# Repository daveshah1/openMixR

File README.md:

# openMixR 4k Mixed Reality Headset

openMixR is an open software/hardware mixed reality headset powered by an Artix-7 FPGA. It combines a high-resolution (4k) virtual reality headset with
4k cameras and a powerful FPGA to provide augmented reality experiences.

## Current Status

Last year as a university group project a low resolution prototype was built, capable of demos
including a 2D Minecraft game and overlaying content from an HDMI input.

PCB design for revision 1 of the 4k version - which this repo is for - has been finished and PCBs have now arrived. FPGA HDL for the cameras has been developed and tested (albeit
  with a different camera model only capable of 4k30, see [this repo](https://github.com/daveshah1/CSI2Rx)), and HDL for basic LCD functionality has been written
and undergone basic testing. To run the display at 4k will require feeding it with VESA DSC compressed video; code for
this is far from complete so I will be using the display at first in a mode where it upscales from 1080p - which
still looks a lot nicer than a native 1080p LCD. Current LCD code is [here](https://github.com/daveshah1/DSITx).

I am now in the process of testing the PCBs and writing a simple AR demo using the LCD and cameras. At present no breaking
issues in the rev 1.0 PCB have arisen although do take note a few minor errata points - see the hardware folder.

I am also working on a custom HLS tool, not yet released, that will be used to create much of the FPGA processing
code that runs on the headset. An early version of this was used for the aforementioned low res demos.

## Hardware Features

The main components of the hardware are:

 - 4k LCD repurposed from Z5 premium (AUO H546UAN01.0 or unknown Sharp part) on a subassembly allowing different LCDs to be used in the future
 - Dual OV16825 cameras, also on a subassembly so other cameras - in particular I am looking into the Sony IMX318 - could be used
 - Artix-7 FPGA (currently XC7A200T-3FBG484E but cheaper variants could be used)
 - Allwinner A64 quad-core ARM applications processor (with basic GPU for 3D rendering)
 - 512MB of DDR3 attached to the FPGA and 1GB attached to the A64 processor
 - WiFi and Bluetooth
 - USB-C for power, data and DisplayPort video

A photo of the assembled mainboard PCB is below:

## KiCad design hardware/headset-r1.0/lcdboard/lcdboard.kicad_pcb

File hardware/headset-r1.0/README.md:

# Hardware for openMixR 1.0

All of the hardware is designed in KiCad 4.0, in the spirit of open source.

- *mainboard* is the headset mainboard, containing the FPGA and processor. It is a 150x90mm 8-layer board
with a minimum track/space of 4mil and a controlled impedance requirement.
- *camboard* is the OV16825 camera subassembly
- *lcdboard* is the Z5 Premium LCD subassembly
- *usbbase* is a board that combines power, USB 2.0 data and Displayport into a USB-C connection,
so openMixR can be used if your computer doesn't support USB-C.

In addition, all of the libraries needed are included. Schematic component libraries are inside the
board folders, with the exception  of *customconn* which is the custom LCD and camera connectors that
interconnect the mainboard and subassemblies. *parts.pretty* contains all of the custom footprints; and *3d*
contains 3D models for many of the components used (for the most part converted from the models provided by their vendors).

PDF schematics are included for all of the boards, if you don't want to install KiCad. Gerbers are also included for all of the boards.

A bill of materials, placement data and impedance control diagrams are also included for the mainboard.

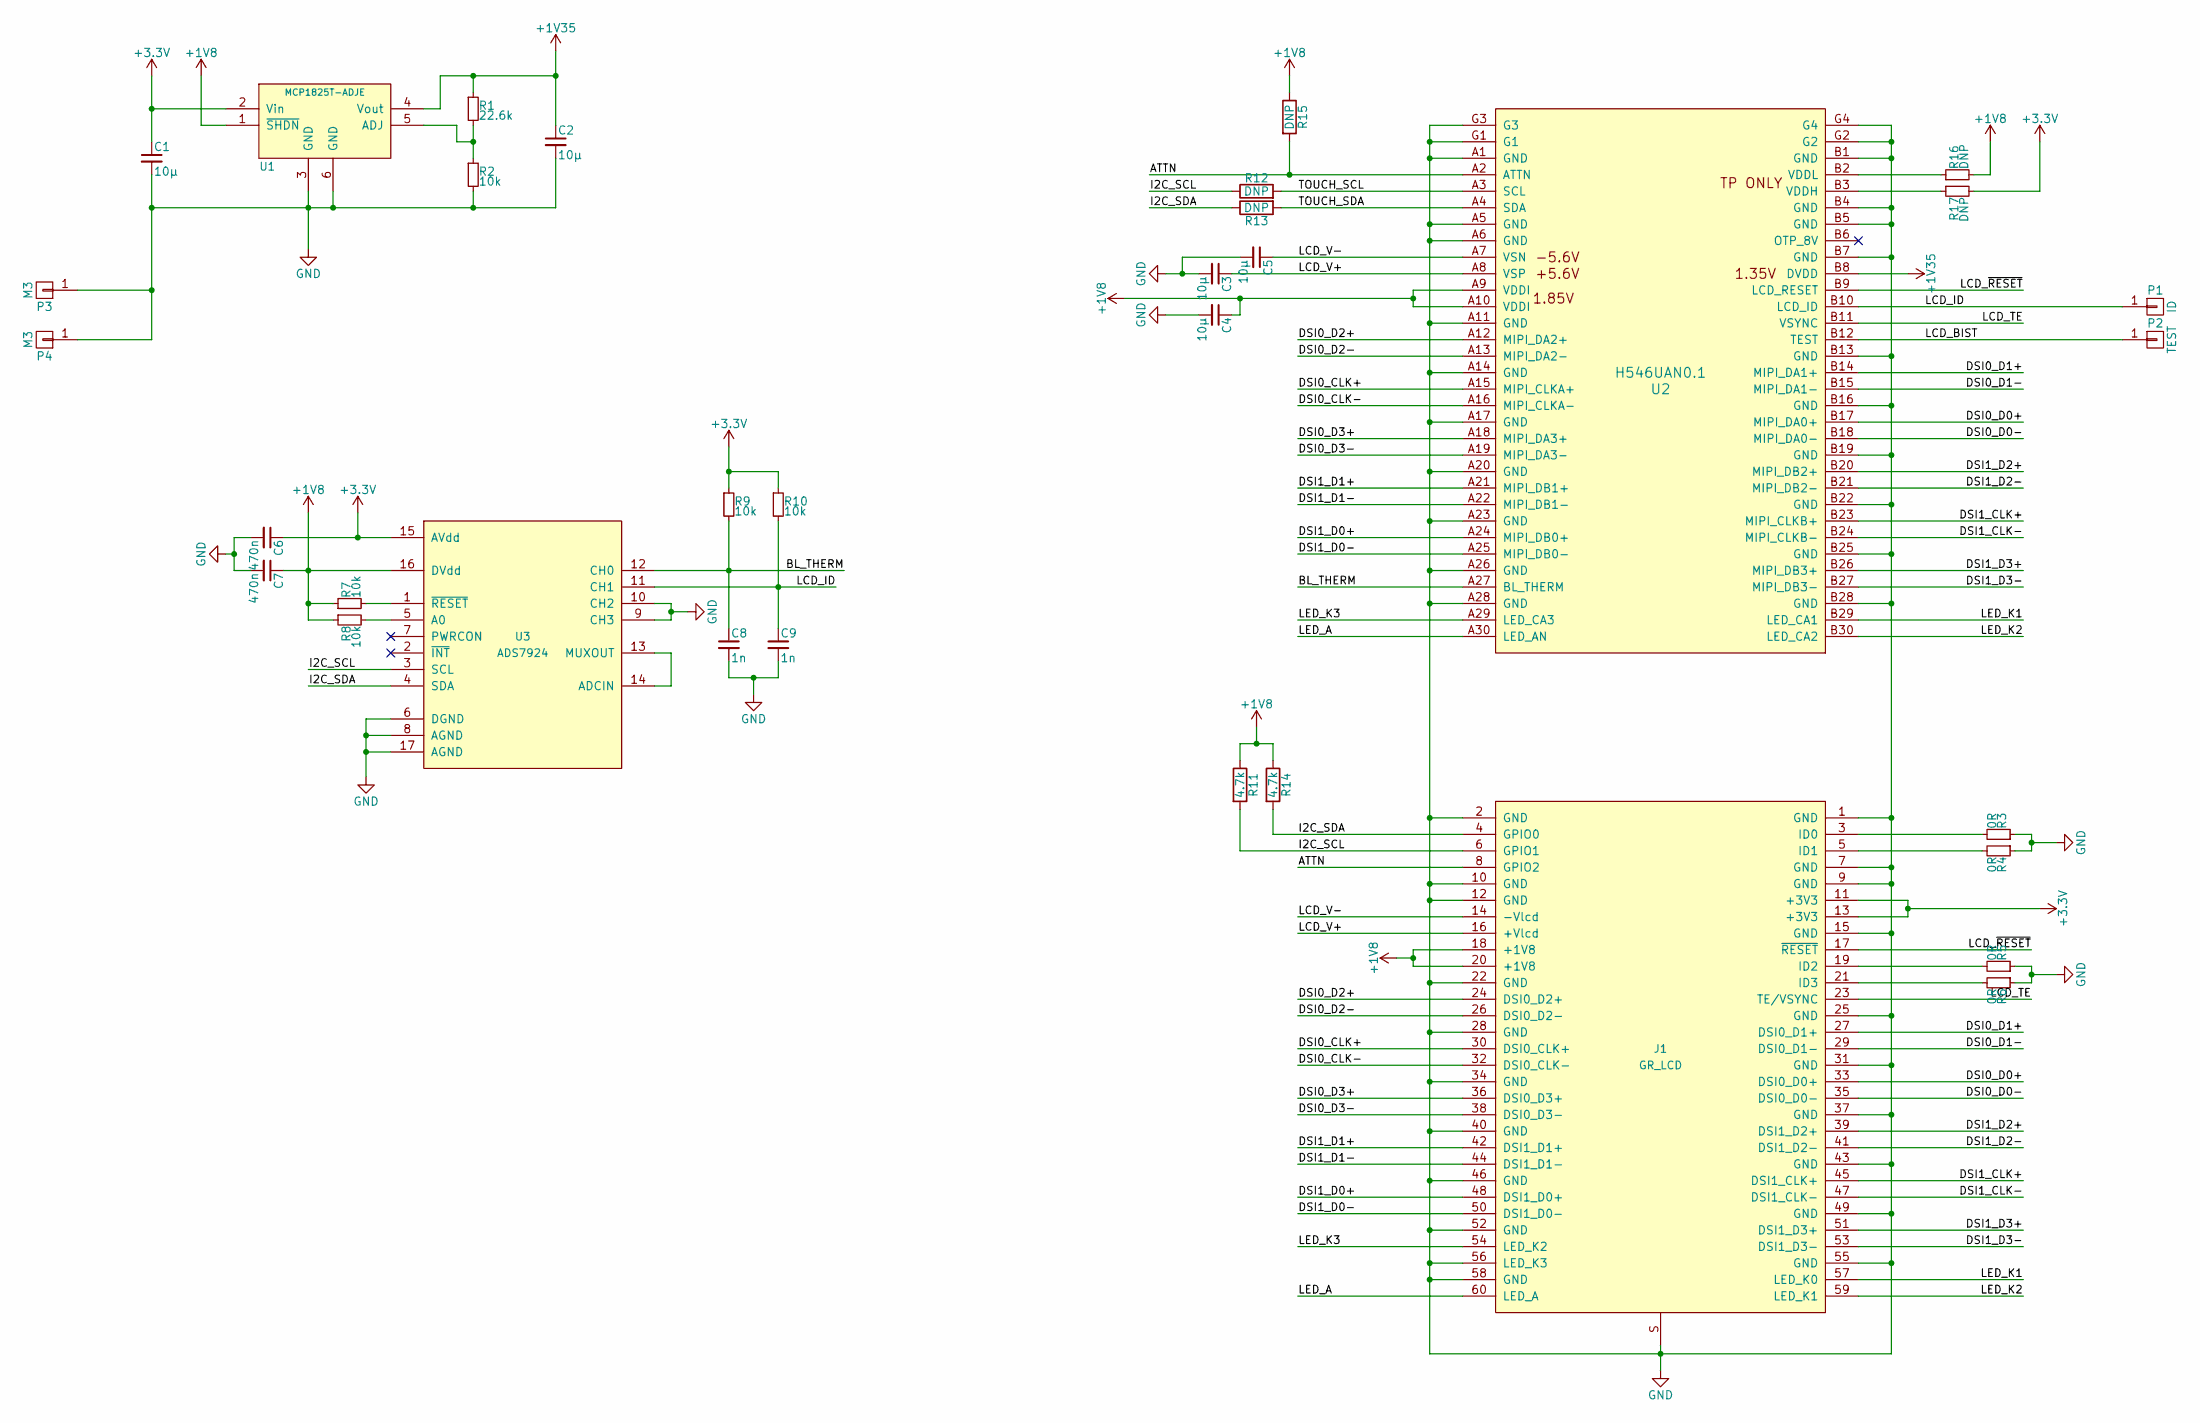
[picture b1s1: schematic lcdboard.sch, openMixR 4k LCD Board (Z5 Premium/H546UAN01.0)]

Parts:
C1, C2, C3, C4, C5: 10µ; C_0805
C6, C7: 470n; C_0402
C8, C9: 1n; C_0402
J1: GR_LCD; DF17(2.0)-60DP-0.5V(57)
P1: ID; Measurement_Point_Square-SMD-Pad_Big
P2: TEST; Measurement_Point_Square-SMD-Pad_Big
P3, P4: M3; M3_HOLE
R1: 22.6k; R_0402
R2, R7, R8, R9, R10: 10k; R_0402
R3, R4, R5, R6: 0R; R_0402
R11, R14: 4.7k; R_0402
R12, R13, R15, R16, R17: DNP; R_0402
U1: MCP1825T-ADJE; SOT-223-6
U2: H546UAN0.1; 60pin-0.35mm
U3: ADS7924; QFN-16-1EP_3x3mm_Pitch0.5mm

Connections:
+1V8: C4.1, C7.1, J1.18 (+1V8), J1.20 (+1V8), R7.1, R8.1, R11.1, R14.1, R15.1, R16.2, U1.1 (~SHDN), U2.A9 (VDDI), U2.A10 (VDDI), U3.16 (DVdd)
+1V35: C2.1, R1.1, U1.4 (Vout), U2.B8 (DVDD)
+3V3: C1.1, C6.1, J1.11 (+3V3), J1.13 (+3V3), R9.1, R10.1, R17.2, U1.2 (Vin), U3.15 (AVdd)
/ATTN: J1.8 (GPIO2), R15.2, U2.A2 (ATTN)
/BL_THERM: C8.1, R9.2, U2.A27 (BL_THERM), U3.12 (CH0)
/DSI0_CLK+: J1.30 (DSI0_CLK+), U2.A15 (MIPI_CLKA+)
/DSI0_CLK-: J1.32 (DSI0_CLK-), U2.A16 (MIPI_CLKA-)
/DSI0_D0+: J1.33 (DSI0_D0+), U2.B17 (MIPI_DA0+)
/DSI0_D0-: J1.35 (DSI0_D0-), U2.B18 (MIPI_DA0-)
/DSI0_D1+: J1.27 (DSI0_D1+), U2.B14 (MIPI_DA1+)
/DSI0_D1-: J1.29 (DSI0_D1-), U2.B15 (MIPI_DA1-)
/DSI0_D2+: J1.24 (DSI0_D2+), U2.A12 (MIPI_DA2+)
/DSI0_D2-: J1.26 (DSI0_D2-), U2.A13 (MIPI_DA2-)
/DSI0_D3+: J1.36 (DSI0_D3+), U2.A18 (MIPI_DA3+)
/DSI0_D3-: J1.38 (DSI0_D3-), U2.A19 (MIPI_DA3-)
/DSI1_CLK+: J1.45 (DSI1_CLK+), U2.B23 (MIPI_CLKB+)
/DSI1_CLK-: J1.47 (DSI1_CLK-), U2.B24 (MIPI_CLKB-)
/DSI1_D0+: J1.48 (DSI1_D0+), U2.A24 (MIPI_DB0+)
/DSI1_D0-: J1.50 (DSI1_D0-), U2.A25 (MIPI_DB0-)
/DSI1_D1+: J1.42 (DSI1_D1+), U2.A21 (MIPI_DB1+)
/DSI1_D1-: J1.44 (DSI1_D1-), U2.A22 (MIPI_DB1-)
/DSI1_D2+: J1.39 (DSI1_D2+), U2.B20 (MIPI_DB2+)
/DSI1_D2-: J1.41 (DSI1_D2-), U2.B21 (MIPI_DB2-)
/DSI1_D3+: J1.51 (DSI1_D3+), U2.B26 (MIPI_DB3+)
/DSI1_D3-: J1.53 (DSI1_D3-), U2.B27 (MIPI_DB3-)
/I2C_SCL: J1.6 (GPIO1), R11.2, R12.1, U3.3 (SCL)
/I2C_SDA: J1.4 (GPIO0), R13.1, R14.2, U3.4 (SDA)
/LCD_BIST: P2.1, U2.B12 (TEST)
/LCD_ID: C9.1, P1.1, R10.2, U2.B10 (LCD_ID), U3.11 (CH1)
/LCD_TE: J1.23 (TE/VSYNC), U2.B11 (VSYNC)
/LCD_V+: C3.1, J1.16 (+Vlcd), U2.A8 (VSP)
/LCD_V-: C5.1, J1.14 (-Vlcd), U2.A7 (VSN)
/LCD_~RESET: J1.17 (~RESET), U2.B9 (LCD_RESET)
/LED_A: J1.60 (LED_A), U2.A30 (LED_AN)
/LED_K1: J1.57 (LED_K0), U2.B29 (LED_CA1)
/LED_K2: J1.59 (LED_K1), U2.B30 (LED_CA2)
/LED_K3: J1.54 (LED_K2), U2.A29 (LED_CA3)
/TOUCH_SCL: R12.2, U2.A3 (SCL)
/TOUCH_SDA: R13.2, U2.A4 (SDA)
GND: C1.2, C2.2, C3.2, C4.2, C5.2, C6.2, C7.2, C8.2, C9.2, J1.1 (GND), J1.2 (GND), J1.7 (GND), J1.9 (GND), J1.10 (GND), J1.12 (GND), J1.15 (GND), J1.22 (GND), J1.25 (GND), J1.28 (GND), J1.31 (GND), J1.34 (GND), J1.37 (GND), J1.40 (GND), J1.43 (GND), J1.46 (GND), J1.49 (GND), J1.52 (GND), J1.55 (GND), J1.56 (LED_K3), J1.58 (GND), J1.S, P3.1, P4.1, R2.2, R3.1, R4.1, R5.1, R6.1, U1.3 (GND), U1.6 (GND), U2.A1 (GND), U2.A5 (GND), U2.A6 (GND), U2.A11 (GND), U2.A14 (GND), U2.A17 (GND), U2.A20 (GND), U2.A23 (GND), U2.A26 (GND), U2.A28 (GND), U2.B1 (GND), U2.B4 (GND), U2.B5 (GND), U2.B7 (GND), U2.B13 (GND), U2.B16 (GND), U2.B19 (GND), U2.B22 (GND), U2.B25 (GND), U2.B28 (GND), U2.G1, U2.G2, U2.G3, U2.G4, U3.6 (DGND), U3.8 (AGND), U3.9 (CH3), U3.10 (CH2), U3.17 (AGND)
unnamed: J1.3 (ID0), R3.2
unnamed: J1.5 (ID1), R4.2
unnamed: J1.19 (ID2), R5.2
unnamed: J1.21 (ID3), R6.2
unnamed: R1.2, R2.1, U1.5 (ADJ)
unnamed: R7.2, U3.1 (~RESET)
unnamed: R8.2, U3.5 (A0)
unnamed: R16.1, U2.B2 (VDDL)
unnamed: R17.1, U2.B3 (VDDH)
unnamed: U3.13 (MUXOUT), U3.14 (ADCIN)

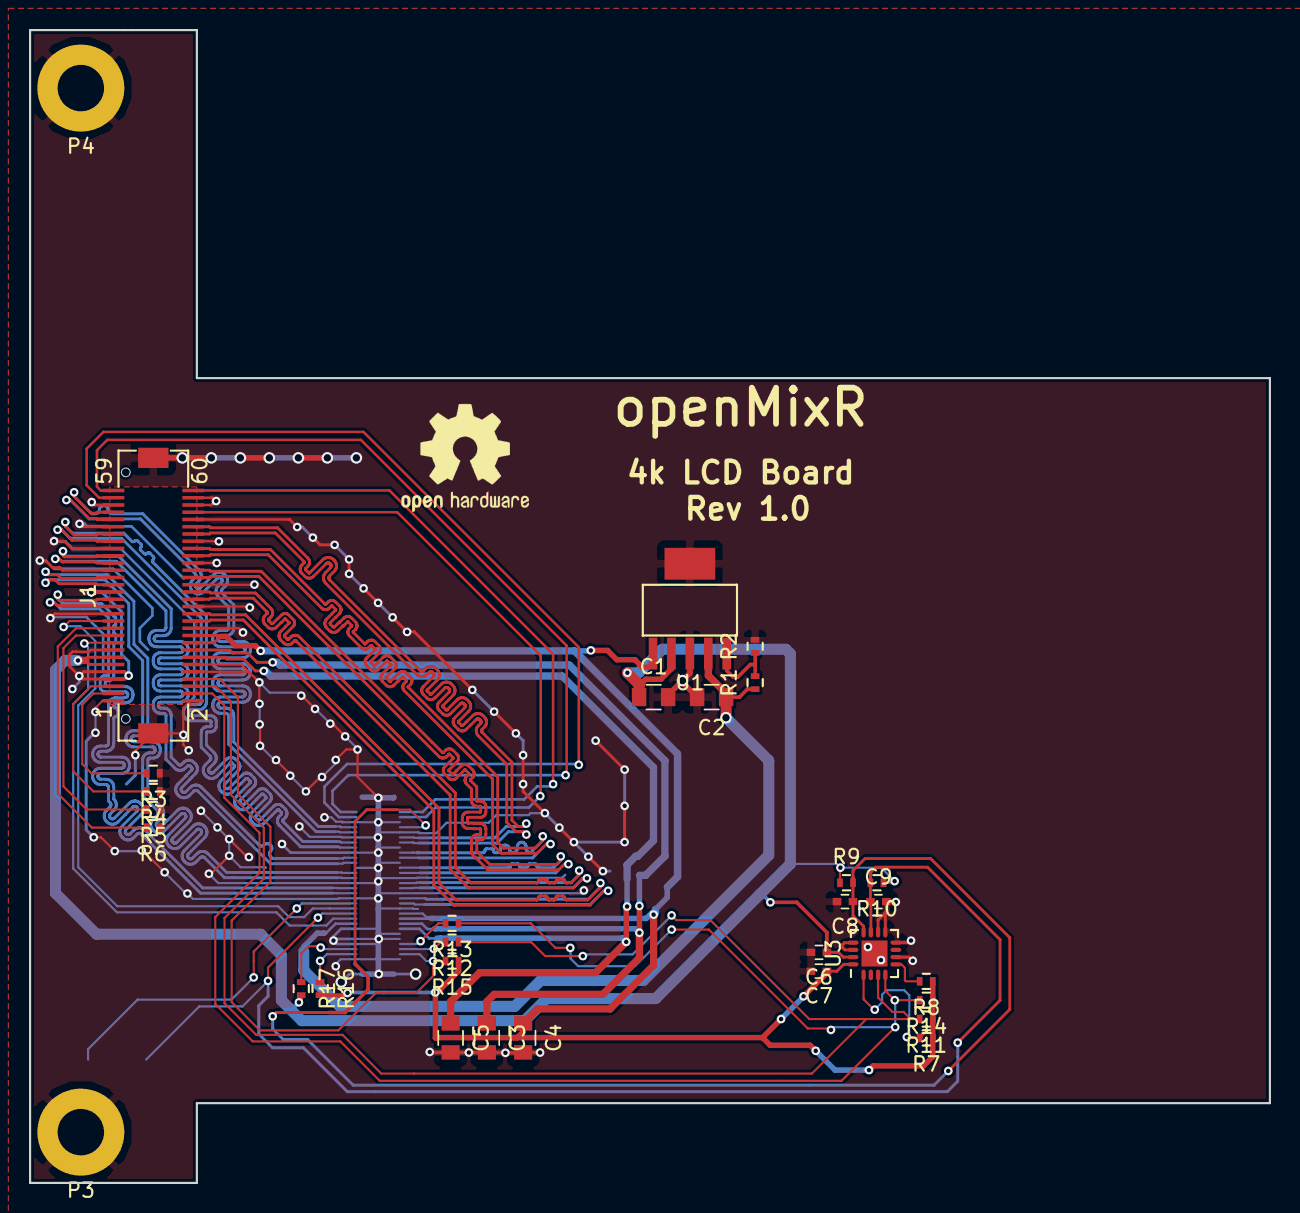
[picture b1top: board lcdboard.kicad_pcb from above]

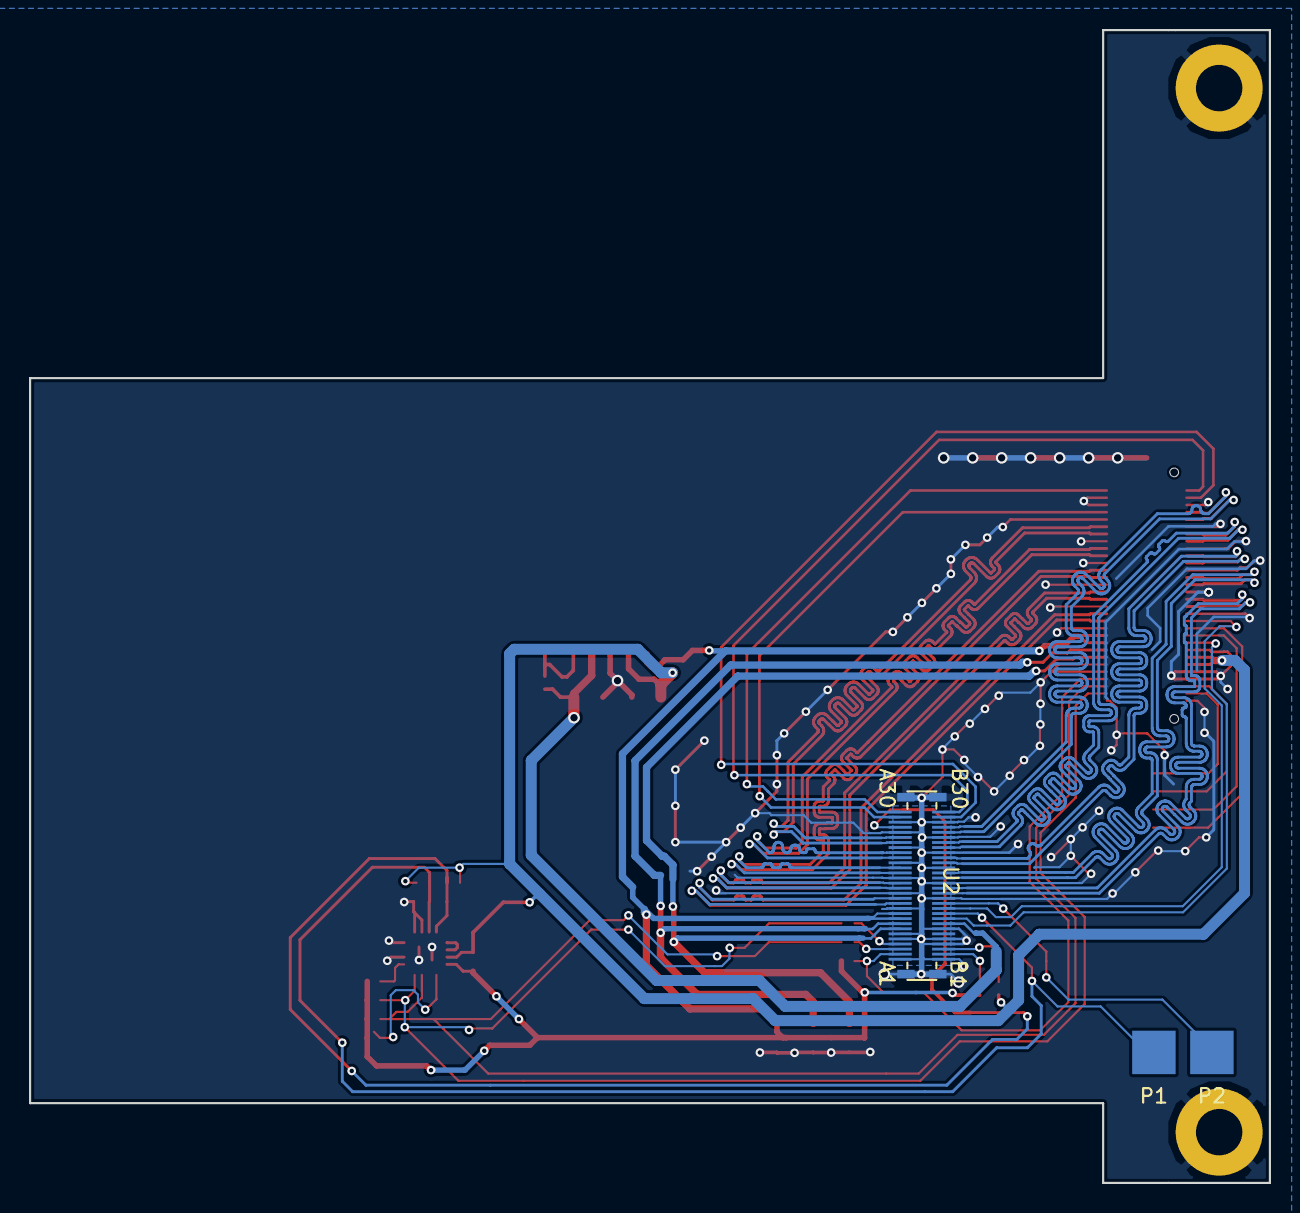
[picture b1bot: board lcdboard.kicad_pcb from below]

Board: 4 copper layers, 85.5 x 79.5 mm, 34 parts (3 on the bottom side), 50 nets.

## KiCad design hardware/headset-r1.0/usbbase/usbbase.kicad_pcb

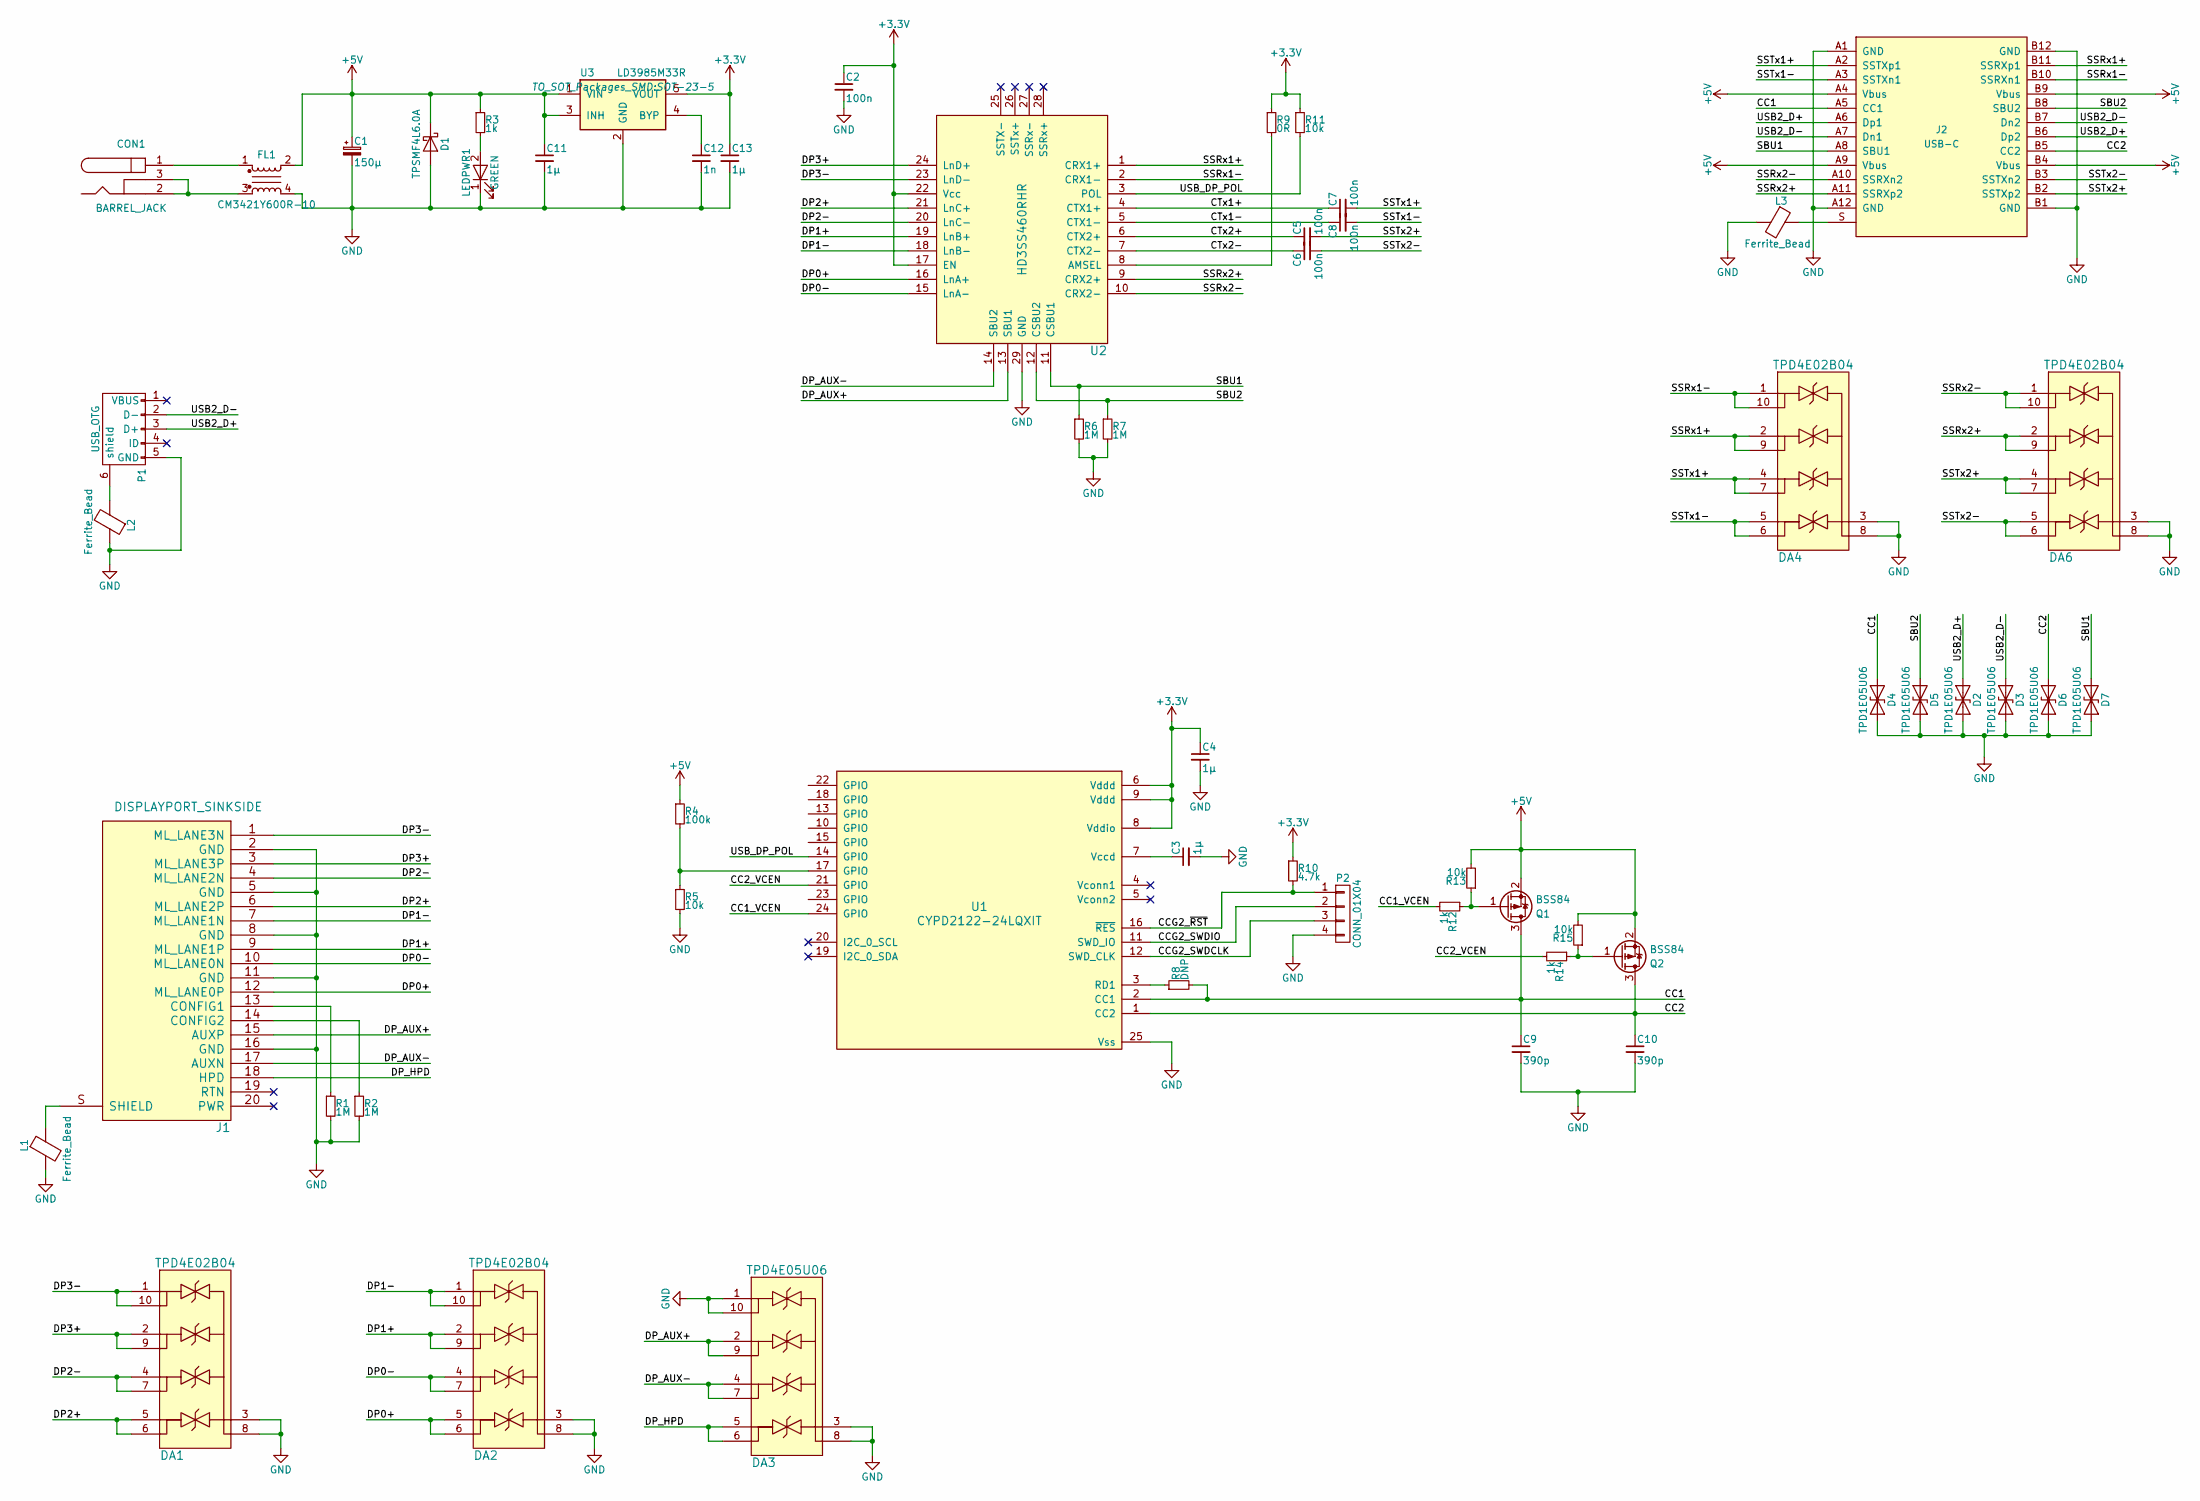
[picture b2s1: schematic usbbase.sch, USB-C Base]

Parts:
C1: 150µ; CP_Elec_6.3x5.8
C2, C5, C6, C7, C8: 100n; C_0402
C3, C4, C11, C13: 1µ; C_0603
C9, C10: 390p; C_0402
C12: 1n; C_0402
CON1: BARREL_JACK
D1: TPSMF4L6.0A; D_SOD-123
D2, D3, D4, D5, D6, D7: TPD1E05U06; X1SON2
DA1, DA2, DA4, DA6: TPD4E02B04; USON10
DA3: TPD4E05U06; USON10
FL1: CM3421Y600R-10
J1: DISPLAYPORT_SINKSIDE; 0472720024
J2: USB-C; USBC-12401548E4#2A
L1, L2, L3: Ferrite_Bead; R_0805
LEDPWR1: GREEN; LED_D3.0mm
P1: USB_OTG; USB_Micro-B
P2: CONN_01X04; Pin_Header_Straight_1x04_Pitch2.54mm
Q1, Q2: BSS84; SOT-23
R1, R2, R6, R7: 1M; R_0402
R3, R12, R14: 1k; R_0402
R4: 100k; R_0402
R5, R11, R13, R15: 10k; R_0402
R8: DNP; R_0402
R9: 0R; R_0402
R10: 4.7k; R_0402
U1: CYPD2122-24LQXIT; QFN-24-1EP_4x4mm_Pitch0.5mm
U2: HD3SS460RHR; WQFN28EP_5.5x3.5mm_Pitch0.5mm
U3: LD3985M33R; SOT-23-5

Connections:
+3V3: C2.1, C4.1, C13.1, R9.1, R10.1, R11.1, U1.6 (Vddd), U1.8 (Vddio), U1.9 (Vddd), U2.17 (EN), U2.22 (Vcc), U3.5 (VOUT)
+5V: C1.1, C11.1, D1.1 (K), FL1.2, J2.A4 (Vbus), J2.A9 (Vbus), J2.B4 (Vbus), J2.B9 (Vbus), Q1.2 (S), Q2.2 (S), R3.1, R4.1, R13.2, R15.2, U3.1 (VIN), U3.3 (INH)
/CC1: C9.1, D4.1 (A1), J2.A5 (CC1), Q1.3 (D), R8.2, U1.2 (CC1)
/CC1_VCEN: R12.2, U1.24 (GPIO)
/CC2: C10.1, D6.1 (A1), J2.B5 (CC2), Q2.3 (D), U1.1 (CC2)
/CC2_VCEN: R14.2, U1.21 (GPIO)
/CCG2_SWDCLK: P2.3, U1.12 (SWD_CLK)
/CCG2_SWDIO: P2.2, U1.11 (SWD_IO)
/CCG2_~RST: P2.1, R10.2, U1.16 (~RES)
/CTx1+: C7.1, U2.4 (CTX1+)
/CTx1-: C8.1, U2.5 (CTX1-)
/CTx2+: C5.1, U2.6 (CTX2+)
/CTx2-: C6.1, U2.7 (CTX2-)
/DP0+: DA2.5 (IO4), DA2.6, J1.12 (ML_LANE0P), U2.16 (LnA+)
/DP0-: DA2.4 (IO3), DA2.7, J1.10 (ML_LANE0N), U2.15 (LnA-)
/DP1+: DA2.2 (IO2), DA2.9, J1.9 (ML_LANE1P), U2.19 (LnB+)
/DP1-: DA2.1 (IO1), DA2.10, J1.7 (ML_LANE1N), U2.18 (LnB-)
/DP2+: DA1.5 (IO4), DA1.6, J1.6 (ML_LANE2P), U2.21 (LnC+)
/DP2-: DA1.4 (IO3), DA1.7, J1.4 (ML_LANE2N), U2.20 (LnC-)
/DP3+: DA1.2 (IO2), DA1.9, J1.3 (ML_LANE3P), U2.24 (LnD+)
/DP3-: DA1.1 (IO1), DA1.10, J1.1 (ML_LANE3N), U2.23 (LnD-)
/DP_AUX+: DA3.2 (IO2), DA3.9, J1.15 (AUXP), U2.13 (SBU1)
/DP_AUX-: DA3.4 (IO3), DA3.7, J1.17 (AUXN), U2.14 (SBU2)
/DP_HPD: DA3.5 (IO4), DA3.6, J1.18 (HPD)
/SBU1: D7.1 (A1), J2.A8 (SBU1), R6.1, U2.11 (CSBU1)
/SBU2: D5.1 (A1), J2.B8 (SBU2), R7.1, U2.12 (CSBU2)
/SSRx1+: DA4.2 (IO2), DA4.9, J2.B11 (SSRXp1), U2.1 (CRX1+)
/SSRx1-: DA4.1 (IO1), DA4.10, J2.B10 (SSRXn1), U2.2 (CRX1-)
/SSRx2+: DA6.2 (IO2), DA6.9, J2.A11 (SSRXp2), U2.9 (CRX2+)
/SSRx2-: DA6.1 (IO1), DA6.10, J2.A10 (SSRXn2), U2.10 (CRX2-)
/SSTx1+: C7.2, DA4.4 (IO3), DA4.7, J2.A2 (SSTXp1)
/SSTx1-: C8.2, DA4.5 (IO4), DA4.6, J2.A3 (SSTXn1)
/SSTx2+: C5.2, DA6.4 (IO3), DA6.7, J2.B2 (SSTXp2)
/SSTx2-: C6.2, DA6.5 (IO4), DA6.6, J2.B3 (SSTXn2)
/USB2_D+: D2.1 (A1), J2.A6 (Dp1), J2.B6 (Dp2), P1.3 (D+)
/USB2_D-: D3.1 (A1), J2.A7 (Dn1), J2.B7 (Dn2), P1.2 (D-)
/USB_DP_POL: R11.2, U1.14 (GPIO), U2.3 (POL)
GND: C1.2, C2.2, C3.2, C4.2, C9.2, C10.2, C11.2, C12.2, C13.2, D1.2 (A), D2.2 (A2), D3.2 (A2), D4.2 (A2), D5.2 (A2), D6.2 (A2), D7.2 (A2), DA1.3 (GND), DA1.8, DA2.3 (GND), DA2.8, DA3.1 (IO1), DA3.3 (GND), DA3.8, DA3.10, DA4.3 (GND), DA4.8, DA6.3 (GND), DA6.8, FL1.4, J1.2 (GND), J1.5 (GND), J1.8 (GND), J1.11 (GND), J1.16 (GND), J2.A1 (GND), J2.A12 (GND), J2.B1 (GND), J2.B12 (GND), L1.2, L2.1, L3.2, LEDPWR1.1 (K), P1.5 (GND), P2.4, R1.2, R2.2, R5.2, R6.2, R7.2, U1.25 (Vss), U2.29 (GND), U3.2 (GND)
unnamed: C3.1, U1.7 (Vccd)
unnamed: C12.1, U3.4 (BYP)
unnamed: CON1.1, FL1.1
unnamed: CON1.2, CON1.3, FL1.3
unnamed: J1.13 (CONFIG1), R1.1
unnamed: J1.14 (CONFIG2), R2.1
unnamed: J1.S (SHIELD), L1.1
unnamed: J2.S, L3.1
unnamed: L2.2, P1.6 (shield)
unnamed: LEDPWR1.2 (A), R3.2
unnamed: Q1.1 (G), R12.1, R13.1
unnamed: Q2.1 (G), R14.1, R15.1
unnamed: R4.2, R5.1, U1.17 (GPIO)
unnamed: R8.1, U1.3 (RD1)
unnamed: R9.2, U2.8 (AMSEL)

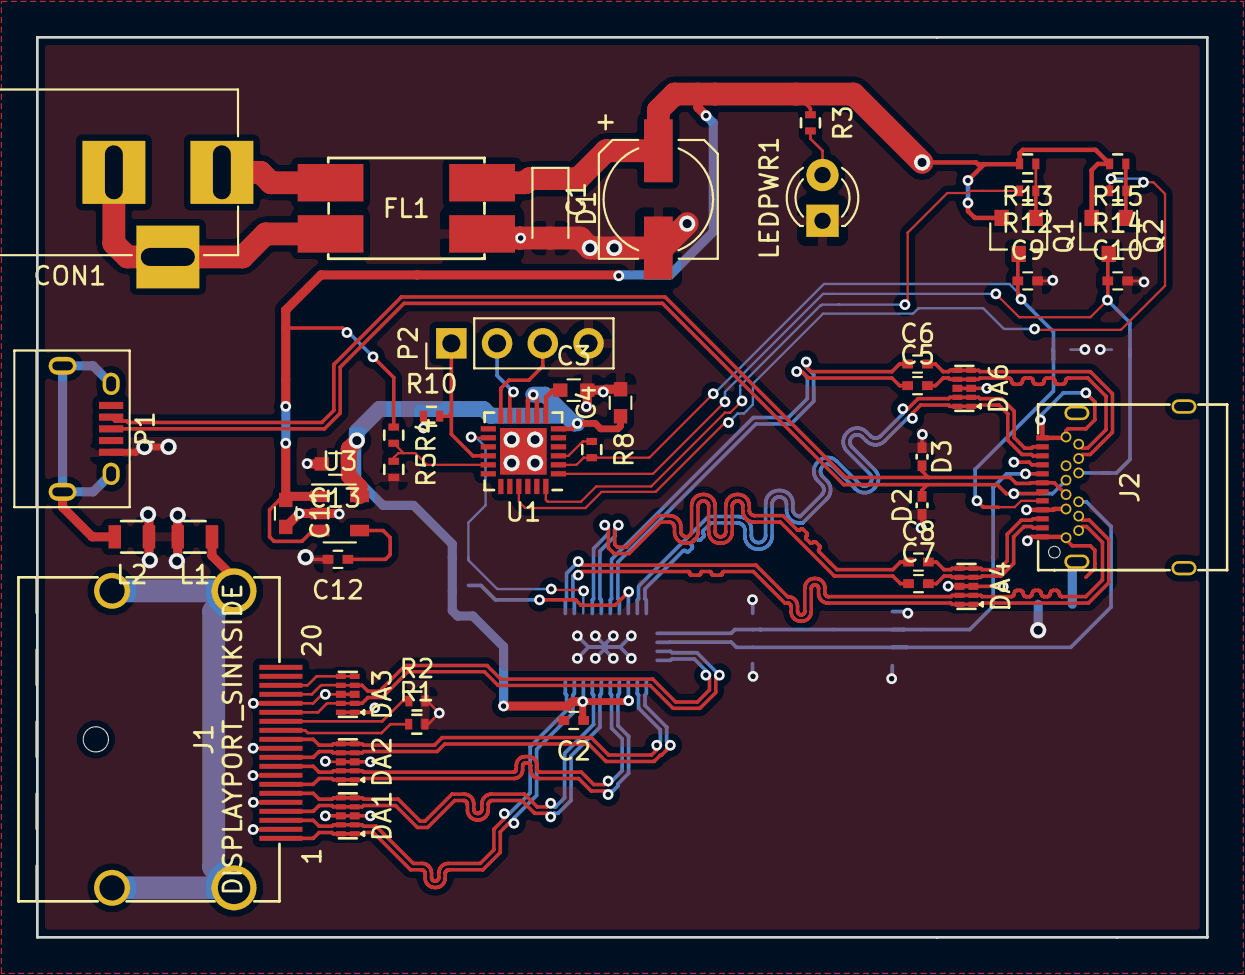
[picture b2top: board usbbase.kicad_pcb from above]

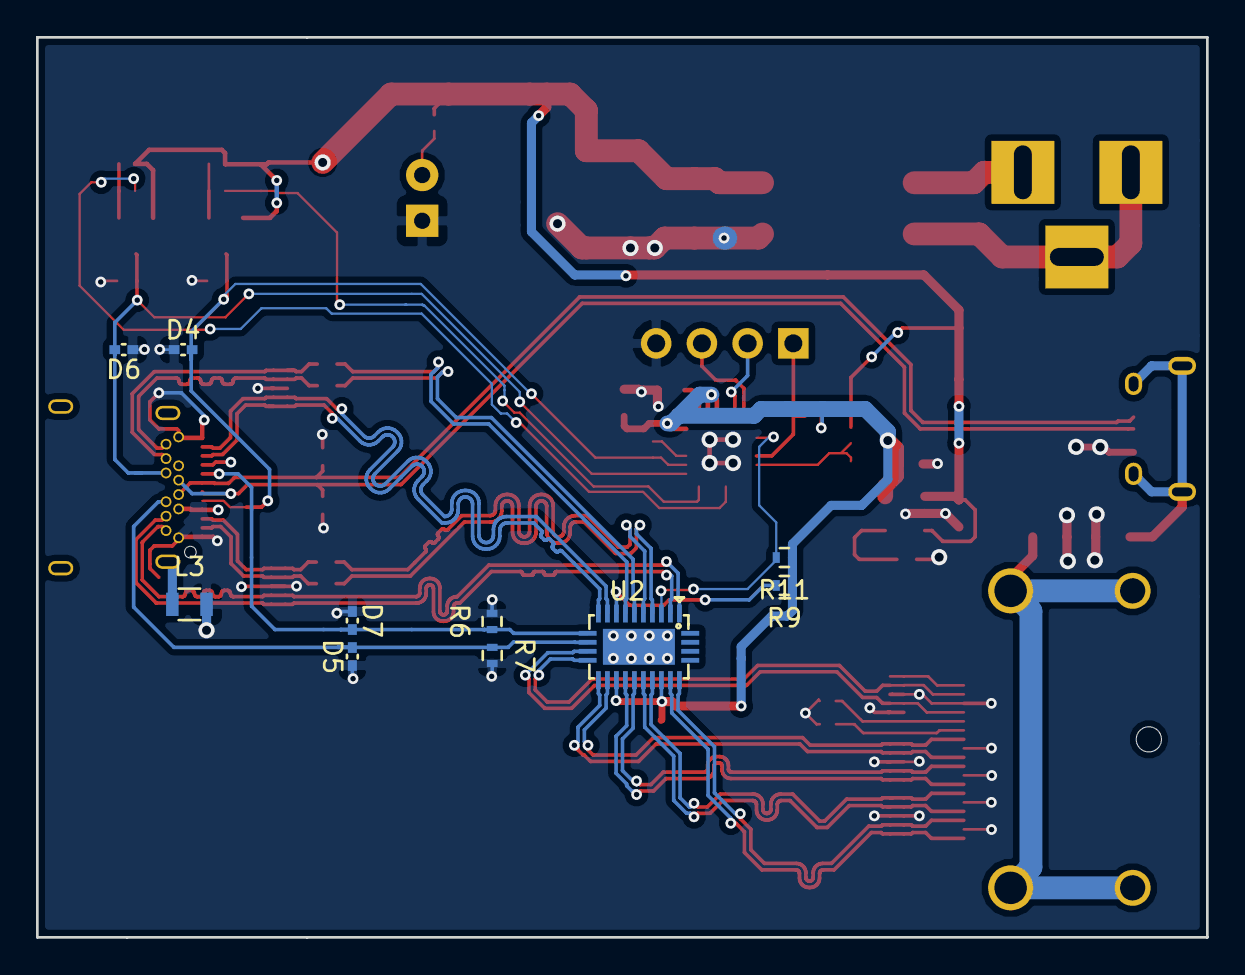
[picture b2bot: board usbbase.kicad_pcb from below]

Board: 4 copper layers, 65.0 x 50.0 mm, 55 parts (10 on the bottom side), 53 nets.

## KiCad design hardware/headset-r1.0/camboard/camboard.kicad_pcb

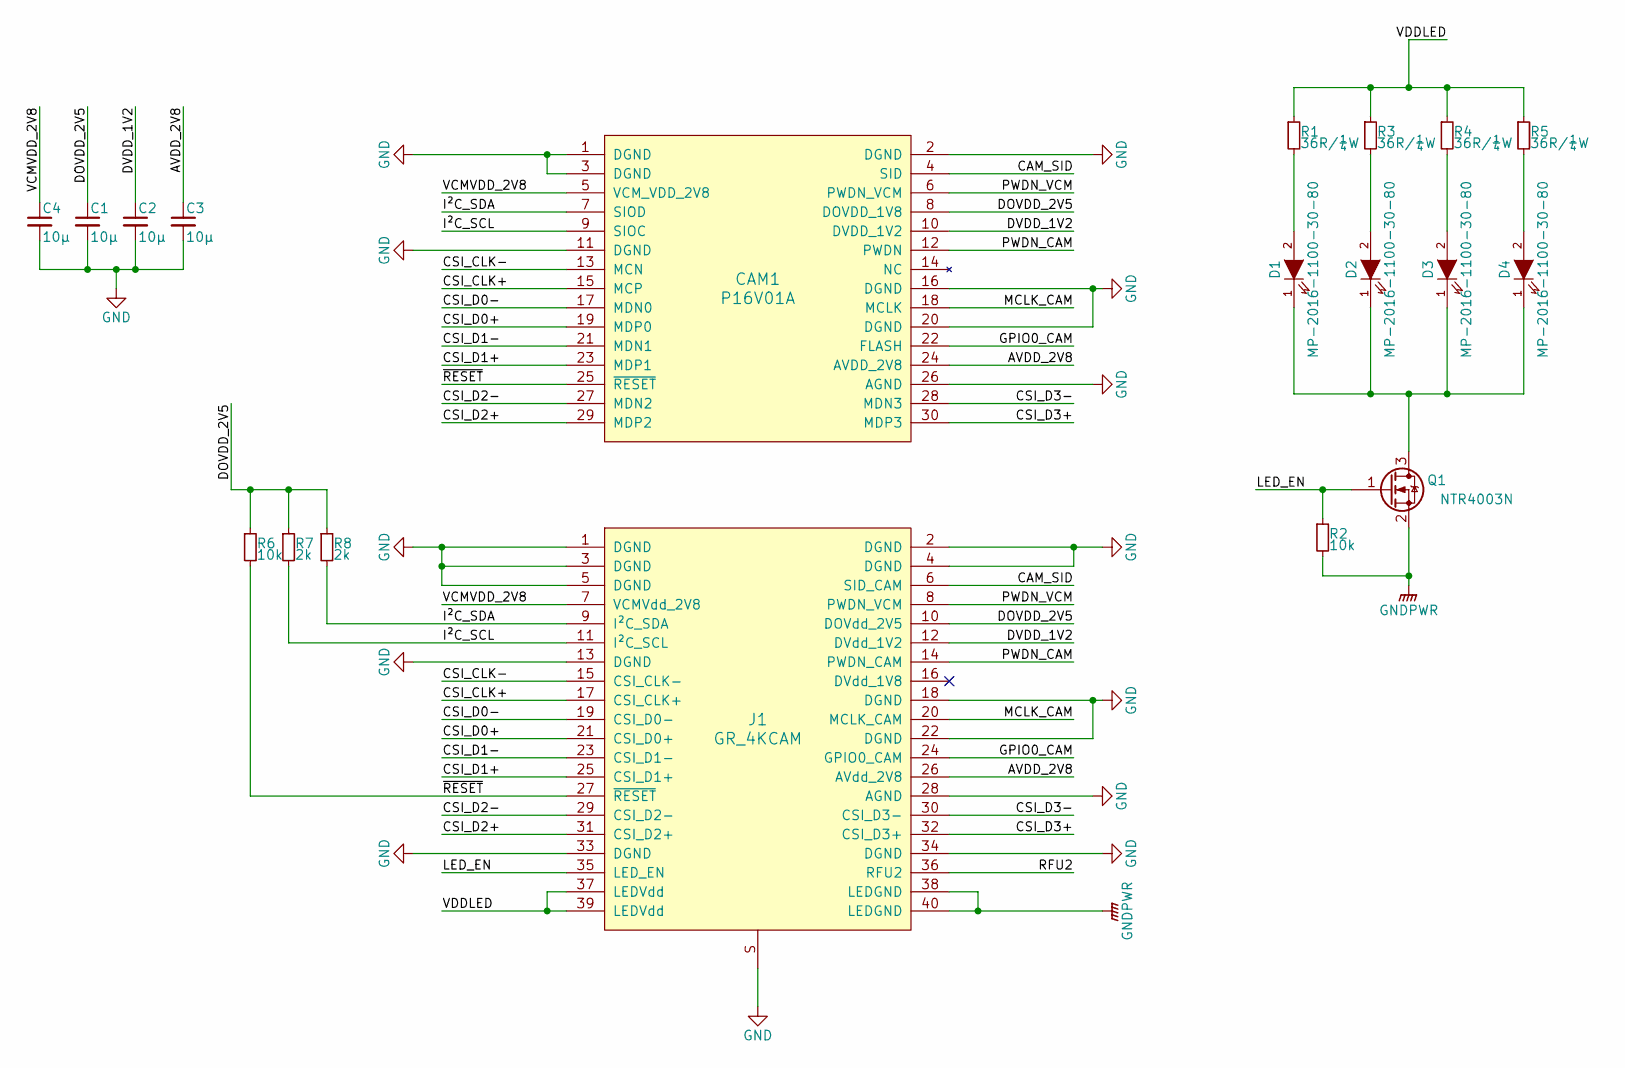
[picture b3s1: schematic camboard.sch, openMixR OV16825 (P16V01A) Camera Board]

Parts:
C1, C2, C3, C4: 10µ; C_0805
CAM1: P16V01A; P16V01A-503304-3040
D1, D2, D3, D4: MP-2016-1100-30-80; LED_MP2016
J1: GR_4KCAM; DF17(4.0)-40DP-0.5V(57)
Q1: NTR4003N; SOT-23
R1, R3, R4, R5: 36R/¼W; R_1206
R2, R6: 10k; R_0402
R7, R8: 2k; R_0402

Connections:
/AVDD_2V8: C3.1, CAM1.24 (AVDD_2V8), J1.26 (AVdd_2V8)
/CAM_SID: CAM1.4 (SID), J1.6 (SID_CAM)
/CSI_CLK+: CAM1.15 (MCP), J1.17 (CSI_CLK+)
/CSI_CLK-: CAM1.13 (MCN), J1.15 (CSI_CLK-)
/CSI_D0+: CAM1.19 (MDP0), J1.21 (CSI_D0+)
/CSI_D0-: CAM1.17 (MDN0), J1.19 (CSI_D0-)
/CSI_D1+: CAM1.23 (MDP1), J1.25 (CSI_D1+)
/CSI_D1-: CAM1.21 (MDN1), J1.23 (CSI_D1-)
/CSI_D2+: CAM1.29 (MDP2), J1.31 (CSI_D2+)
/CSI_D2-: CAM1.27 (MDN2), J1.29 (CSI_D2-)
/CSI_D3+: CAM1.30 (MDP3), J1.32 (CSI_D3+)
/CSI_D3-: CAM1.28 (MDN3), J1.30 (CSI_D3-)
/DOVDD_2V5: C1.1, CAM1.8 (DOVDD_1V8), J1.10 (DOVdd_2V5), R6.1, R7.1, R8.1
/DVDD_1V2: C2.1, CAM1.10 (DVDD_1V2), J1.12 (DVdd_1V2)
/GPIO0_CAM: CAM1.22 (FLASH), J1.24 (GPIO0_CAM)
/I²C_SCL: CAM1.9 (SIOC), J1.11 (I²C_SCL), R7.2
/I²C_SDA: CAM1.7 (SIOD), J1.9 (I²C_SDA), R8.2
/LED_EN: J1.35 (LED_EN), Q1.1 (G), R2.1
/MCLK_CAM: CAM1.18 (MCLK), J1.20 (MCLK_CAM)
/PWDN_CAM: CAM1.12 (PWDN), J1.14 (PWDN_CAM)
/PWDN_VCM: CAM1.6 (PWDN_VCM), J1.8 (PWDN_VCM)
/VCMVDD_2V8: C4.1, CAM1.5 (VCM_VDD_2V8), J1.7 (VCMVdd_2V8)
/VDDLED: J1.37 (LEDVdd), J1.39 (LEDVdd), R1.1, R3.1, R4.1, R5.1
/~RESET: CAM1.25 (~RESET), J1.27 (~RESET), R6.2
GND: C1.2, C2.2, C3.2, C4.2, CAM1.1 (DGND), CAM1.2 (DGND), CAM1.3 (DGND), CAM1.11 (DGND), CAM1.16 (DGND), CAM1.20 (DGND), CAM1.26 (AGND), J1.1 (DGND), J1.2 (DGND), J1.3 (DGND), J1.4 (DGND), J1.5 (DGND), J1.13 (DGND), J1.18 (DGND), J1.22 (DGND), J1.28 (AGND), J1.33 (DGND), J1.34 (DGND), J1.S
GNDPWR: J1.38 (LEDGND), J1.40 (LEDGND), Q1.2 (S), R2.2
unnamed: D1.1 (K), D2.1 (K), D3.1 (K), D4.1 (K), Q1.3 (D)
unnamed: D1.2 (A), R1.2
unnamed: D2.2 (A), R3.2
unnamed: D3.2 (A), R4.2
unnamed: D4.2 (A), R5.2

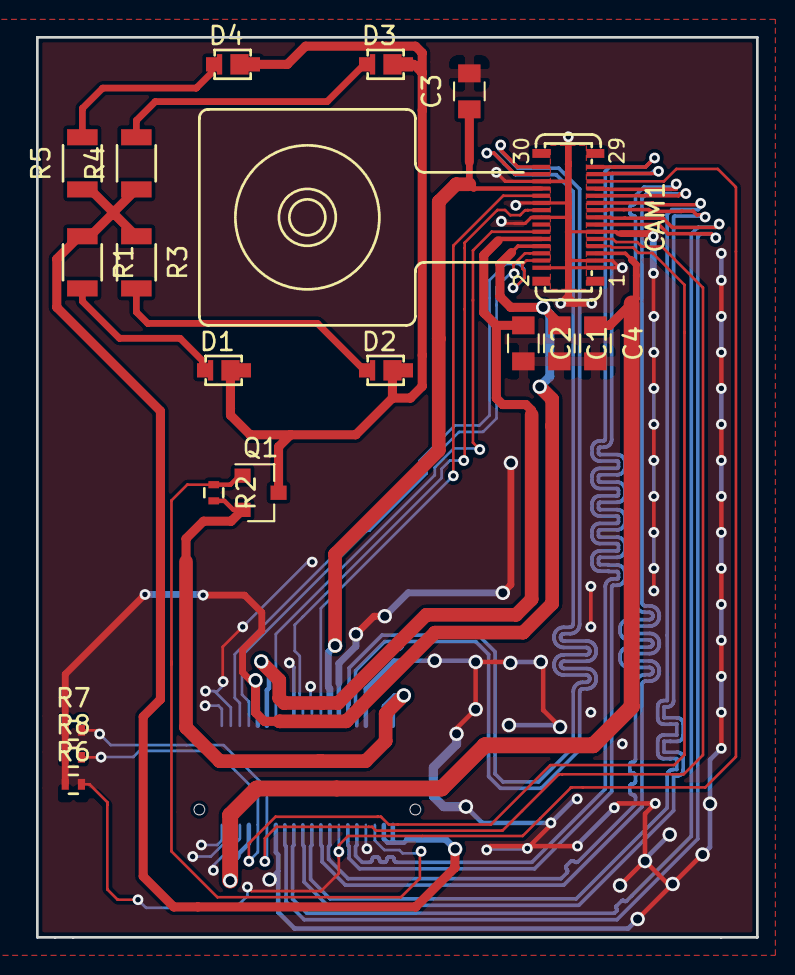
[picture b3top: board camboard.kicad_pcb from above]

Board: 4 copper layers, 40.0 x 50.0 mm, 19 parts (1 on the bottom side), 31 nets.

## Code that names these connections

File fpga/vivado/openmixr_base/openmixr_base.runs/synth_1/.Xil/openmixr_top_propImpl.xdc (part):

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set_property src_info {type:XDC file:1 line:312 export:INPUT save:INPUT read:READ} [current_design]
set_property PACKAGE_PIN AB16 [get_ports dp_aux_p]
set_property src_info {type:XDC file:1 line:313 export:INPUT save:INPUT read:READ} [current_design]
set_property PACKAGE_PIN L13 [get_ports dp_hpd]
set_property src_info {type:XDC file:1 line:361 export:INPUT save:INPUT read:READ} [current_design]
set_property PACKAGE_PIN D20 [get_ports {dphy0_hs_clk[1]}]
set_property src_info {type:XDC file:1 line:362 export:INPUT save:INPUT read:READ} [current_design]
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set_property src_info {type:XDC file:1 line:482 export:INPUT save:INPUT read:READ} [current_design]
set_property PACKAGE_PIN F18 [get_ports {lcd_gpio[2]}]
set_property src_info {type:XDC file:1 line:486 export:INPUT save:INPUT read:READ} [current_design]
set_property PACKAGE_PIN AB3 [get_ports {lcd_id[0]}]
set_property src_info {type:XDC file:1 line:487 export:INPUT save:INPUT read:READ} [current_design]
set_property PACKAGE_PIN AB2 [get_ports {lcd_id[1]}]
set_property src_info {type:XDC file:1 line:488 export:INPUT save:INPUT read:READ} [current_design]
set_property PACKAGE_PIN AB1 [get_ports {lcd_id[2]}]
set_property src_info {type:XDC file:1 line:489 export:INPUT save:INPUT read:READ} [current_design]
set_property PACKAGE_PIN AA1 [get_ports {lcd_id[3]}]
set_property src_info {type:XDC file:1 line:494 export:INPUT save:INPUT read:READ} [current_design]
set_property PACKAGE_PIN G20 [get_ports lcd_psu_scl]
set_property src_info {type:XDC file:1 line:495 export:INPUT save:INPUT read:READ} [current_design]
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set_property src_info {type:XDC file:1 line:496 export:INPUT save:INPUT read:READ} [current_design]
set_property PACKAGE_PIN C18 [get_ports lcd_reset_b]
set_property src_info {type:XDC file:1 line:500 export:INPUT save:INPUT read:READ} [current_design]
set_property PACKAGE_PIN F21 [get_ports lcd_te]
set_property src_info {type:XDC file:1 line:502 export:INPUT save:INPUT read:READ} [current_design]
set_property PACKAGE_PIN J21 [get_ports {rgb_led[0]}]
set_property src_info {type:XDC file:1 line:503 export:INPUT save:INPUT read:READ} [current_design]
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
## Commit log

2017-02-14 Add LICENSE
2017-02-14 Add README with project outline
2017-02-14 Add current hardware designs
2017-02-16 README updates
2017-04-25 Readme update
2017-05-04 Add LCD and camera submodules
2017-05-04 Create Vivado project and import existing sources
2017-05-05 Define top level IO ports
2017-05-10 Add display driver to top level design
2017-05-10 Hardware has arrived
2017-05-10 Add Gerbers for other boards, README tweaks
2017-05-11 Add camera driver to top level
2017-05-11 Add button input driver
2017-05-11 More camera integration
2017-05-11 Create PLLs, start pin assignment
2017-05-12 Dual camera reset sequencing module
2017-05-13 Finish pin assignments
2017-05-13 Get design to compile
2017-05-28 Tweaks 1
2017-05-31 Tweak IO and PLL to move towards working DSI
2017-10-03 More display debugging
2017-10-07 Misc tweaks
